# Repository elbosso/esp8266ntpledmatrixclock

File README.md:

# esp8266ntpledmatrixclock

<!---

--->

This repository actually combines what i learned from building
https://github.com/elbosso/sonoffSocket
and 
https://github.com/elbosso/esp8266epaperdoorsign
with an MAX7119 8x8 Led Matrix (well - actually four of them) and
a photo resistor.

The data for connecting with your wifi is located in a header file named `wifi_security.h` that i did
not commit for obvious reasons. Its contents look something like the contents of the example named
`wifi_security_h.example`:

```
#ifndef WIFISECURITY_H
#define WIFISECURITY_H

char wifi_ssid[]="<wifi_ssid>";
char wifi_pwd[]="<wifi_pwd>";
char wifi_ssid_cell_ap[]="<wifi_ssid_cell_ap>";
char wifi_pwd_cell_ap[]="<wifi_pwd_cell_ap>";

#endif /* WIFISECURITY_H */
```

The define `AT_HOME` is used to control what NTP-server should be used: The source code presumes a local NTP-server 
exists at IP-address `192.168.10.2` if
`AT_HOME` is set to 1 - if this is not so, it currently asks `2.de.pool.ntp.org` for the time.

The define `AT_HOME` also decides which pair of WIFI credentials are to be used.

Instructions for setting up the arduino IDE to actually be able to transfer the code to a Wemos D1 (clone) can be found [here](https://averagemaker.com/2018/03/wemos-d1-mini-setup.html)

And so we have a nifty little clock...

## Important Update

This project continues the work originally started in this project: https://github.com/elbosso/ESP8266-WiFi-Marquee

The new features include:

* offering a HTTP interface for specifying arbitrary text that is displayed using running text
* offering an MQTT interface for the same reasons
* allowing to switch the display of the time on and off both via HTTP and MQTT
* possibility to use arbitrarily many chained display modules

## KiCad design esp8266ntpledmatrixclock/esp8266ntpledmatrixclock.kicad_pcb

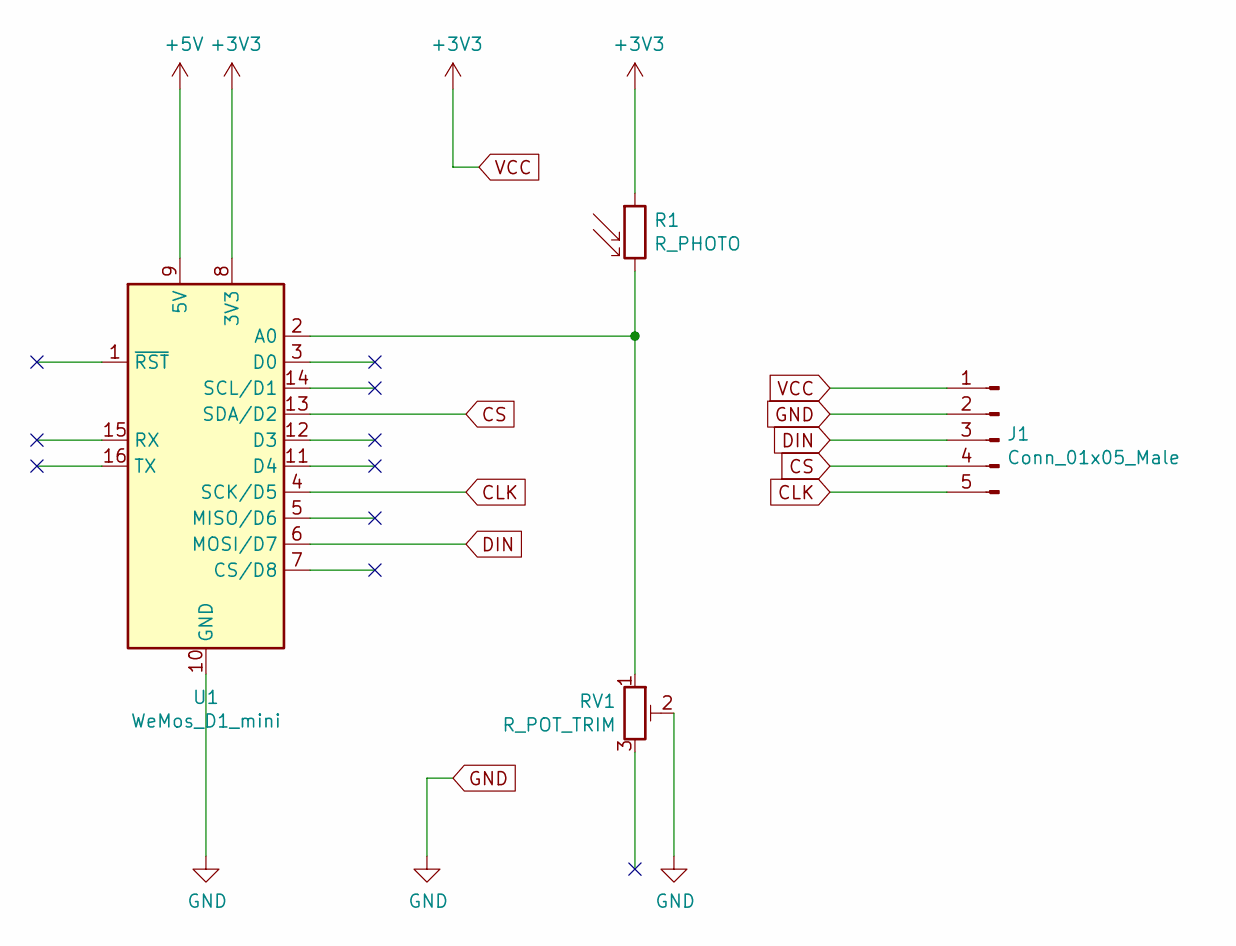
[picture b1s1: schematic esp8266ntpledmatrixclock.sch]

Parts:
J1: Conn_01x05_Male; PinHeader_1x05_P2.54mm_Vertical
R1: R_PHOTO; R_Axial_DIN0309_L9.0mm_D3.2mm_P12.70mm_Horizontal
RV1: R_POT_TRIM; Potentiometer_Bourns_3386F_Vertical
U1: WeMos_D1_mini; WEMOS_D1_mini_light

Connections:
+5V: U1.9 (5V)
CLK: J1.5, U1.4 (SCK/D5)
CS: J1.4, U1.13 (SDA/D2)
DIN: J1.3, U1.6 (MOSI/D7)
GND: J1.2, RV1.2, U1.10 (GND)
unnamed: R1.2, RV1.1, U1.2 (A0)
VCC: J1.1, R1.1, U1.8 (3V3)

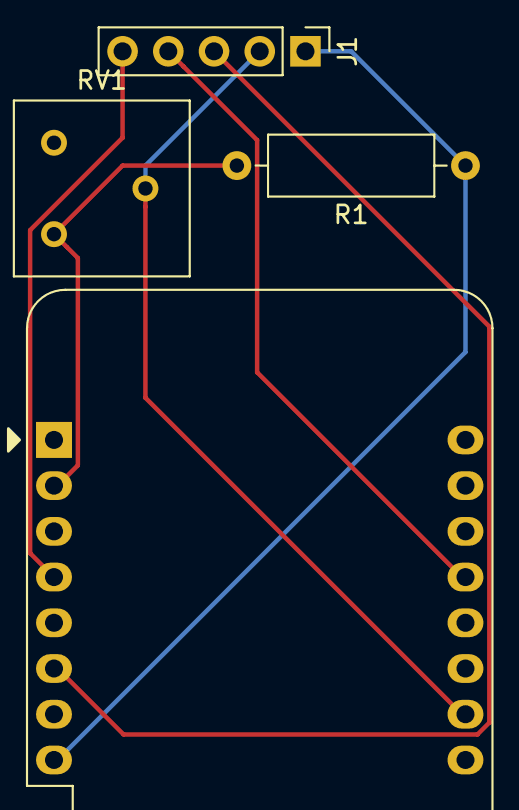
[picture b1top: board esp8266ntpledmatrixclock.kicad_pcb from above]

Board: 2 copper layers, 4 parts (0 on the bottom side), 6 nets.

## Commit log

2018-09-17 initial checkin
2018-10-21 new animation mode
2018-10-21 another new animation mode
2018-10-21 some new animation modes added
2019-01-04 BADGES ADDED
2020-03-01 documentation efforts
2020-03-01 schematics added
2020-03-01 added instructions for getting the code onto hardware...
2020-03-01 schematics added as pdf
2020-03-01 naming mistake
2020-03-08 now the clock is ready for any number of segments...
2020-03-08 now one can display short messages on the display of the clock controlled by a web form the esp offers
2020-03-08 slight improvement of the look of the form
2020-03-09 now it is possible to switch of/switch on the clock display between messages from the html form all new features (scrolling messages, switching the clock display off and on) can now be used by sendin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
2020-03-10 new font for marquee - complete with lower case letters and umlauts
2020-03-10 failure to connect to mqtt broker no longer renders the clock useless...
2020-03-10 problem with the persistent colon fixed
2020-03-10 added value for resistor in voltage divider measuring ambient light
2020-03-10 minor code cleanup, default is now a configuration with 8 8x8 ledmatrix modules in one line
2020-03-19 fixes #5, fixes #6
2020-05-27 re elbosso/manmuesstemal#59
2020-06-13 fixes #7
2020-06-13 fixes #9
2020-09-24 small bug fixed that influenced the command for switching off the display of the time: it would be switched off as soon as the minute changed
